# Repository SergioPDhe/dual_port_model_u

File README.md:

# dual_port_model_u
 modification of the model-u circuit to add a second USB port for easier D+/D- connections
 
 Based on Crane's Model-U: https://github.com/Crane1195/Model-U

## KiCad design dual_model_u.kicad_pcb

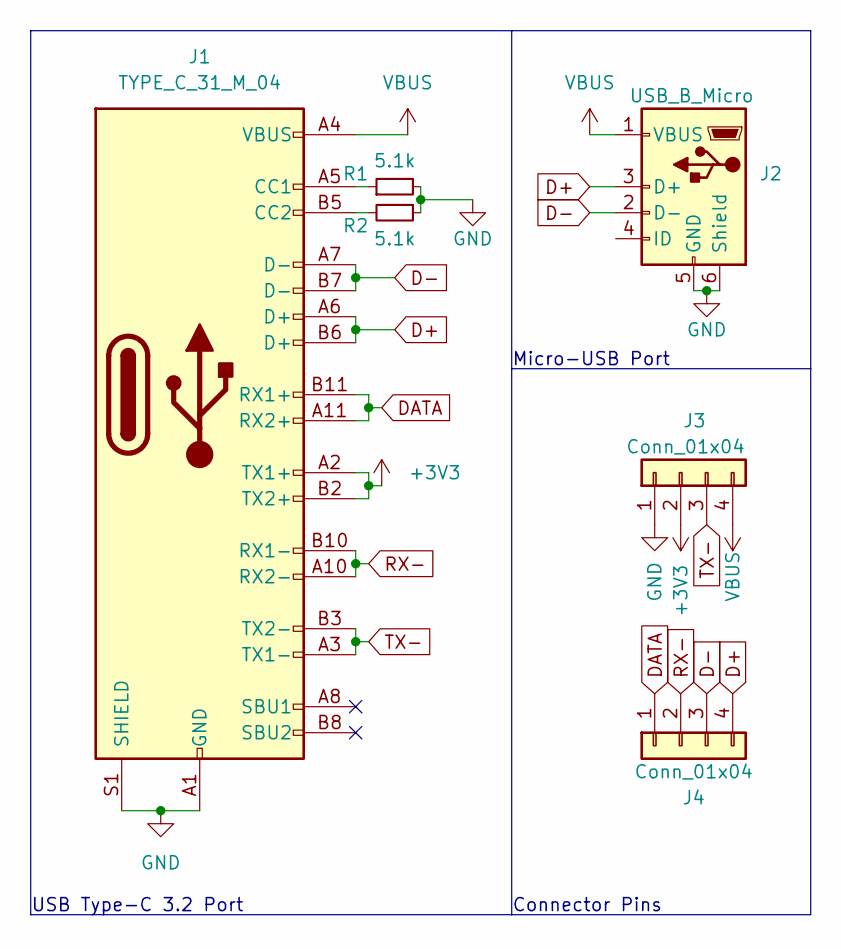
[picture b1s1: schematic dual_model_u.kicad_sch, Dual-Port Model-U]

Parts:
J1: TYPE_C_31_M_04; HRO_TYPE-C-31-M-04
J2: USB_B_Micro; USB_Micro-B_Amphenol_10118194_Horizontal
J3, J4: Conn_01x04; PinSocket_1x04_P2.54mm_Vertical
R1, R2: 5.1k; R_0603_1608Metric

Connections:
+3V3: J1.A2 (TX1+), J1.B2 (TX2+), J3.2
D+: J1.A6 (D+), J1.B6 (D+), J2.3 (D+), J4.4
D-: J1.A7 (D-), J1.B7 (D-), J2.2 (D-), J4.3
DATA: J1.A11 (RX2+), J1.B11 (RX1+), J4.1
GND: J1.A1 (GND), J1.A12 (GND), J1.B1 (GND), J1.B12 (GND), J1.S1 (SHIELD), J2.5 (GND), J2.6 (Shield), J3.1, R1.2, R2.1
unnamed: J1.A5 (CC1), R1.1
unnamed: J1.B5 (CC2), R2.2
RX-: J1.A10 (RX2-), J1.B10 (RX1-), J4.2
TX-: J1.A3 (TX1-), J1.B3 (TX2-), J3.3
VBUS: J1.A4 (VBUS), J1.A9 (VBUS), J1.B4 (VBUS), J1.B9 (VBUS), J2.1 (VBUS), J3.4

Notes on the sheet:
USB Type-C 3.2 Port
Connector Pins
Micro-USB Port

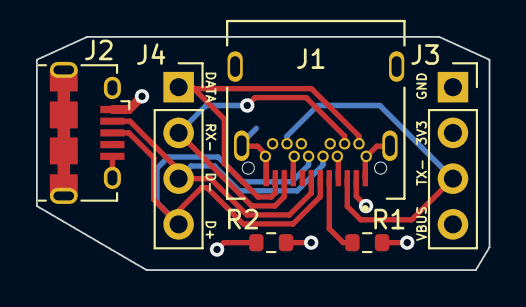
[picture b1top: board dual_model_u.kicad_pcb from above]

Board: 4 copper layers, 25.1 x 13.0 mm, 6 parts (0 on the bottom side), 10 nets.

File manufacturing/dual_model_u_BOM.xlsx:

Comment | Designator | Footprint | JLBPCB part #
TYPE_C_31_M_04 | J1 | Connector_USB_C_3_2:HRO_TYPE-C-31-M-04 | C129018
USB_B_Micro | J2 | Connector_USB:USB_Micro-B_Amphenol_10118194_Horizontal | C132563
5.1k | R1, R2 | R0603 | C23186

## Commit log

2022-07-25 Added KICAD symbol and footprint
2022-07-25 Cleaned up sheets
